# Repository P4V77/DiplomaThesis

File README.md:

# Modular Current Source

## Specifications
### v2.0
- **U<sub>IN</sub>** = 12 - 48V
- **I<sub>OUT_DC</sub>** = &plusmn;10 A (max output power limited by PTC fuses to 144W/48V, current is load and input voltage dependent)
- **I<sub>OUT_AC</sub>** = &plusmn;10 A (0 A DC offset, max output power limited by PTC fuses to 144W/48V, current is load and input voltage dependent)
- **Waveforms:**
  - Harmonic with settable DC offset
  - Square with settable DC offset and Duty Cycle <0,100> %
  - Triangle with settable DC offset
- **Default settings:**  
  - I = 0 A
  - DC offset = 0
  - Duty Cycle = 50%
  - Waveform LUT not initialized (DC output set by default)
- **L<sub>load</sub>** at least 100&micro;H, preferably more than 150 &micro;H
- **Communication:**
  - **CAN FD**
    - Baudrate: 500 kb/s
  - **UART**
    - Baudrate: 921 600 Bd
    - 8 data bits
    - 1 stop bit
    - No parity

#### Set New ID
- **Command:** `ID`
- **Data:** Desired ID (0-250)
- **Description:** Sets a new ID for the current source.

**Example:**
```
1ID5  // Sets the ID of the current source to 5
```

#### Set Current
- **Command:** `I`
- **Data:** Desired current as a signed integer in mA (plus sign not allowed)
- **Description:** Sets the current for DC output and amplitude for AC output.

**Examples:**
```
1I650    // Sets current to 650mA for source ID 1
3I-5000  // Sets current to -5A for source ID 3
```

#### Choosing AC/DC Output
- **Commands:**
  - `D` - DC output
  - `A` - AC output
- **Data:**
  - `1` - Enable AC/DC output
  - `0` - Disable output
- **Note:** For AC output, waveform must be chosen first (see "Set Waveform").

**Examples:**
```
1D1  // Enables DC output for source ID 1
4A1  // Enables AC output for source ID 4
```

#### Set Waveform
- **Commands:**
  - `H` - Harmonic waveform
  - `S` - Square waveform
  - `T` - Triangle waveform
- **Data:** Desired frequency in Hz (unsigned integer)
- **Notes:**
  - Zero DC offset, duty cycle defaults to 50% (square)
  - Max waveform frequency from MoSeZ: **6000 Hz** (actual max depends on load)

**Examples:**
```
1H50     // Sets harmonic waveform at 50 Hz for source ID 1
3S6000   // Sets square waveform at 6000 Hz for source ID 3
2T1000   // Sets triangle waveform at 1000 Hz for source ID 2
```

#### Set DC Offset
- **Command:** `O`
- **Data:** Desired DC current offset of alternating current (signed integer in mA, plus sign not allowed)
- **Applicable for:** All AC waveforms

**Examples:**
```
1O650   // Sets DC offset to 650mA for source ID 1
3O-5000 // Sets DC offset to -5A for source ID 3
```

#### Set Duty Cycle (Square Wave Only)
- **Command:** `C`
- **Data:** Desired duty cycle in % (1-99)

**Examples:**
```
1C40  // Sets duty cycle to 40% for source ID 1
3C80  // Sets duty cycle to 80% for source ID 3
```

#### Set Ramp Time (Square Wave Only)
- **Command:** `RT`
- **Data:** Ramp time in percents (unsigned integer)

**Examples:**
```
1RT50  // Sets ramp time of square waveform to 50% (makes triangle waveform) for source ID 1
2RT10 // Sets ramp time of square waveform to 10% for source ID 2
```

#### Set Phase Shift
- **Command:** `F`
- **Data:** Phase shift in degrees (unsigned integer, 0-359)

**Examples:**
```
1F90   // Sets phase shift to 90° for source ID 1
3F180  // Sets phase shift to 180° for source ID 3
```

#### Position Control
- **Command:** `P`
- **Data:**
  - `1` - Enable position control
  - `0` - Disable output
- **Description:** Enables position control for a linear vibrator with position feedback.

**Example:**
```
9P1  // Enables position control for source ID 9
```

#### Set Position Amplitude
- **Command:** `R`
- **Data:** Position amplitude in micrometers (unsigned integer)
- **Constraints:**
  - **Max position offset + amplitude** ≤ 8 mm
  - **Min position offset - amplitude** ≥ 1 mm

**Examples:**
```
1R3500  // Sets position amplitude to 3.5 mm for source ID 1
5R1000  // Sets position amplitude to 1 mm for source ID 5
```

#### Set Position Offset
- **Command:** `V`
- **Data:** Position offset in micrometers (unsigned integer)
- **Constraints:** Same as "Set Position Amplitude"

**Examples:**
```
1V4000  // Sets position offset to 4 mm for source ID 1
5V7000  // Sets position offset to 7 mm for source ID 5
```

#### Start Logging Position to CAN
- **Command:** `CL`
- **Data:**
  - `1` - Start logging
  - `0` - Stop logging
- **Description:** Sends position data every millisecond (ID, actual position, requested position).

**Example:**
```
1CL1  // Starts position logging for source ID 1
```

#### Define Sequence (Whole Period)
- **Command:** `SP`
- **Data:** Duration of the sequence step in whole periods 
- **Description:** Starts defining a new/next sequence command step with a duration measured in whole periods of the waveform.

**Example:**
```
1SP5  // Starts a new sequence step with a duration of 5 whole periods for source ID 1
```

#### Define Sequence (Half Period)
- **Command:** `SH`
- **Data:** Duration of the sequence step in half periods 
- **Description:** Starts defining a new/next sequence command step with a duration measured in half periods of the waveform.

**Example:**
```
2SH10 // Starts a new sequence step with a duration of 10 half periods for source ID 2
```

#### Define Sequence (Milliseconds)
- **Command:** `SW`
- **Data:** Duration of the sequence step in milliseconds 
- **Description:** Starts defining a new/next sequence command step with a duration measured in milliseconds.
**Example:**
```
4SW100 // Starts a new sequence step with a duration of 100 milliseconds for source ID 4
```

#### Stop Filling Current Sequence
- **Command:** `SF`
- **Data:** No data required (value is ignored)
- **Description:** Stops adding commands to the currently being defined sequence step.

**Example:**
```
1SF  // Stops filling the current sequence step for source ID 1
```

#### Start Sequence
- **Command:** `ST`
- **Data:** Any value accepted
- **Description:** Starts the execution of a pre-configured sequence of commands.

**Example:**
```
1ST  // Starts the stored sequence for source ID 1
```

#### Clear All Sequences
- **Command:** `SC`
- **Data:** Any value accepted
- **Description:** Clears all pre-configured sequences of commands.

**Example:**
```
3SC  // Clears all stored sequences for source ID 3
```

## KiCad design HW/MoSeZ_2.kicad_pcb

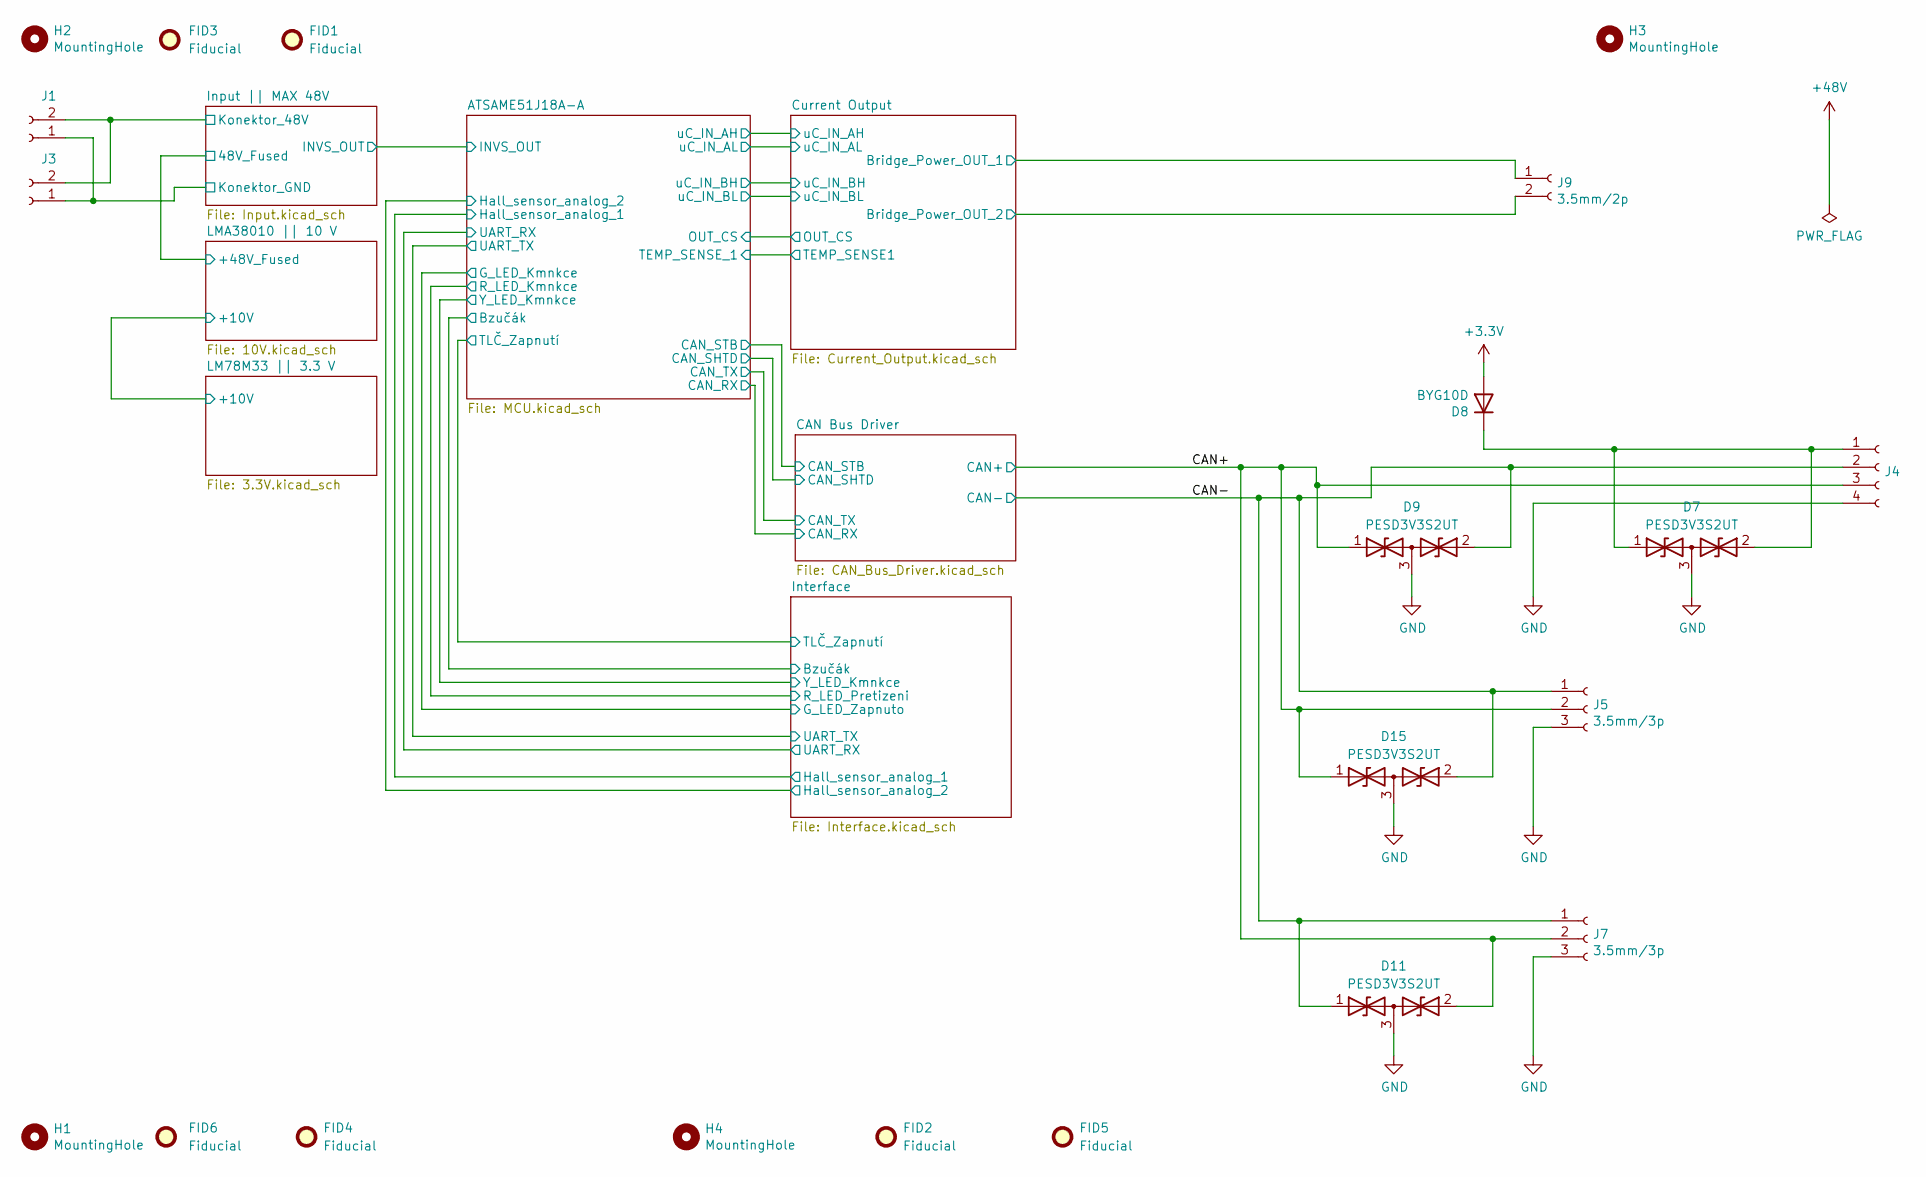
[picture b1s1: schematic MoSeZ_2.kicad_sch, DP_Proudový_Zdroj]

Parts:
D7, D9, D11, D15: PESD3V3S2UT; SOT-23
D8: BYG10D; D_SMA
FID1, FID2, FID3, FID4, FID5, FID6: Fiducial; Fiducial_1mm_Mask2mm
H1, H2, H3, H4: MountingHole; MountingHole_3.5mm_Pad
J1, J3, J9: 3.5mm/2p; PhoenixContact_MC_1,5_2-G-3.5_1x02_P3.50mm_Horizontal
J4: 2.54/4p; PinHeader_1x04_P2.54mm_Vertical
J5, J7: 3.5mm/3p; PhoenixContact_MC_1,5_3-G-3.5_1x03_P3.50mm_Horizontal

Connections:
+3.3V: D8.2 (A); also elsewhere on the board
+48V: J1.2, J3.2; also elsewhere on the board
/CAN+: D9.1 (A1), D11.2 (A2), D15.1 (A1), J4.3, J5.2, J7.2; also elsewhere on the board
/CAN-: D9.2 (A2), D11.1 (A1), D15.2 (A2), J4.2, J5.1, J7.1; also elsewhere on the board
/Current Output/Bridge_Power_OUT_2: J9.2; also elsewhere on the board
/Current Output/DRIVER_1_SW: J9.1; also elsewhere on the board
GND: D7.3 (common), D9.3 (common), D11.3 (common), D15.3 (common), J1.1, J3.1, J4.4, J5.3, J7.3; also elsewhere on the board
unnamed: D7.1 (A1), D7.2 (A2), D8.1 (K), J4.1

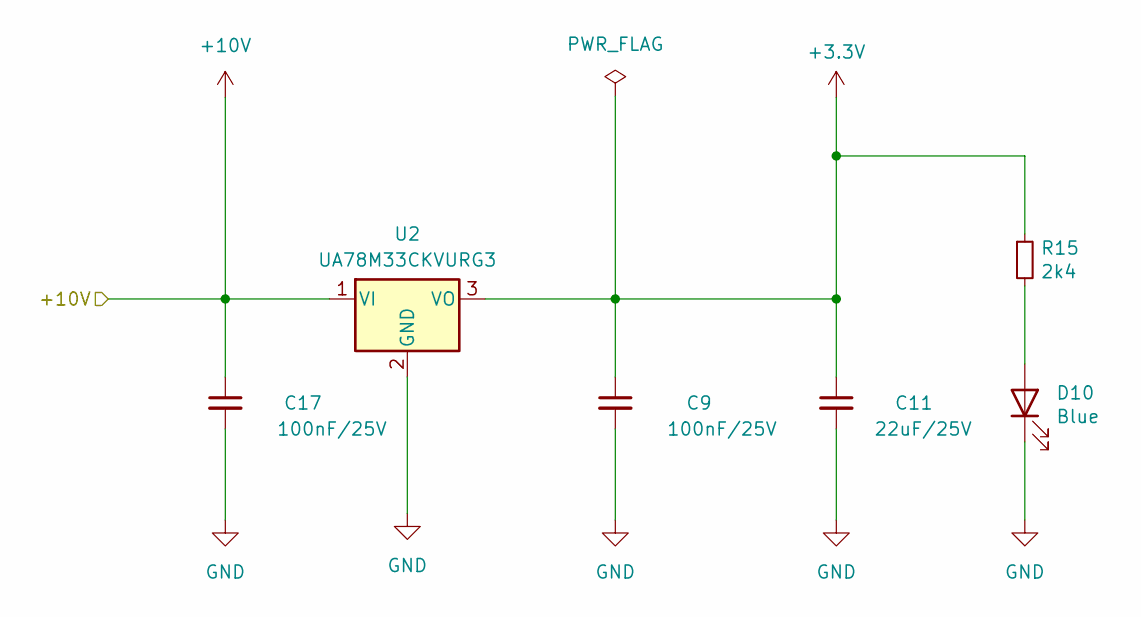
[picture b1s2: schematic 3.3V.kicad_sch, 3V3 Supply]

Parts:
C9, C17: 100nF/25V; C_0603_1608Metric
C11: 22uF/25V; C_0805_2012Metric
D10: Blue; D_0603_1608Metric
R15: 2k4; R_0603_1608Metric
U2: UA78M33CKVURG3; TO-252-2

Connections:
+3.3V: C9.1, C11.1, R15.1, U2.3 (VO); also elsewhere on the board
+10V: C17.1, U2.1 (VI); also elsewhere on the board
GND: C9.2, C11.2, C17.2, D10.1 (K), U2.2 (GND); also elsewhere on the board
unnamed: D10.2 (A), R15.2

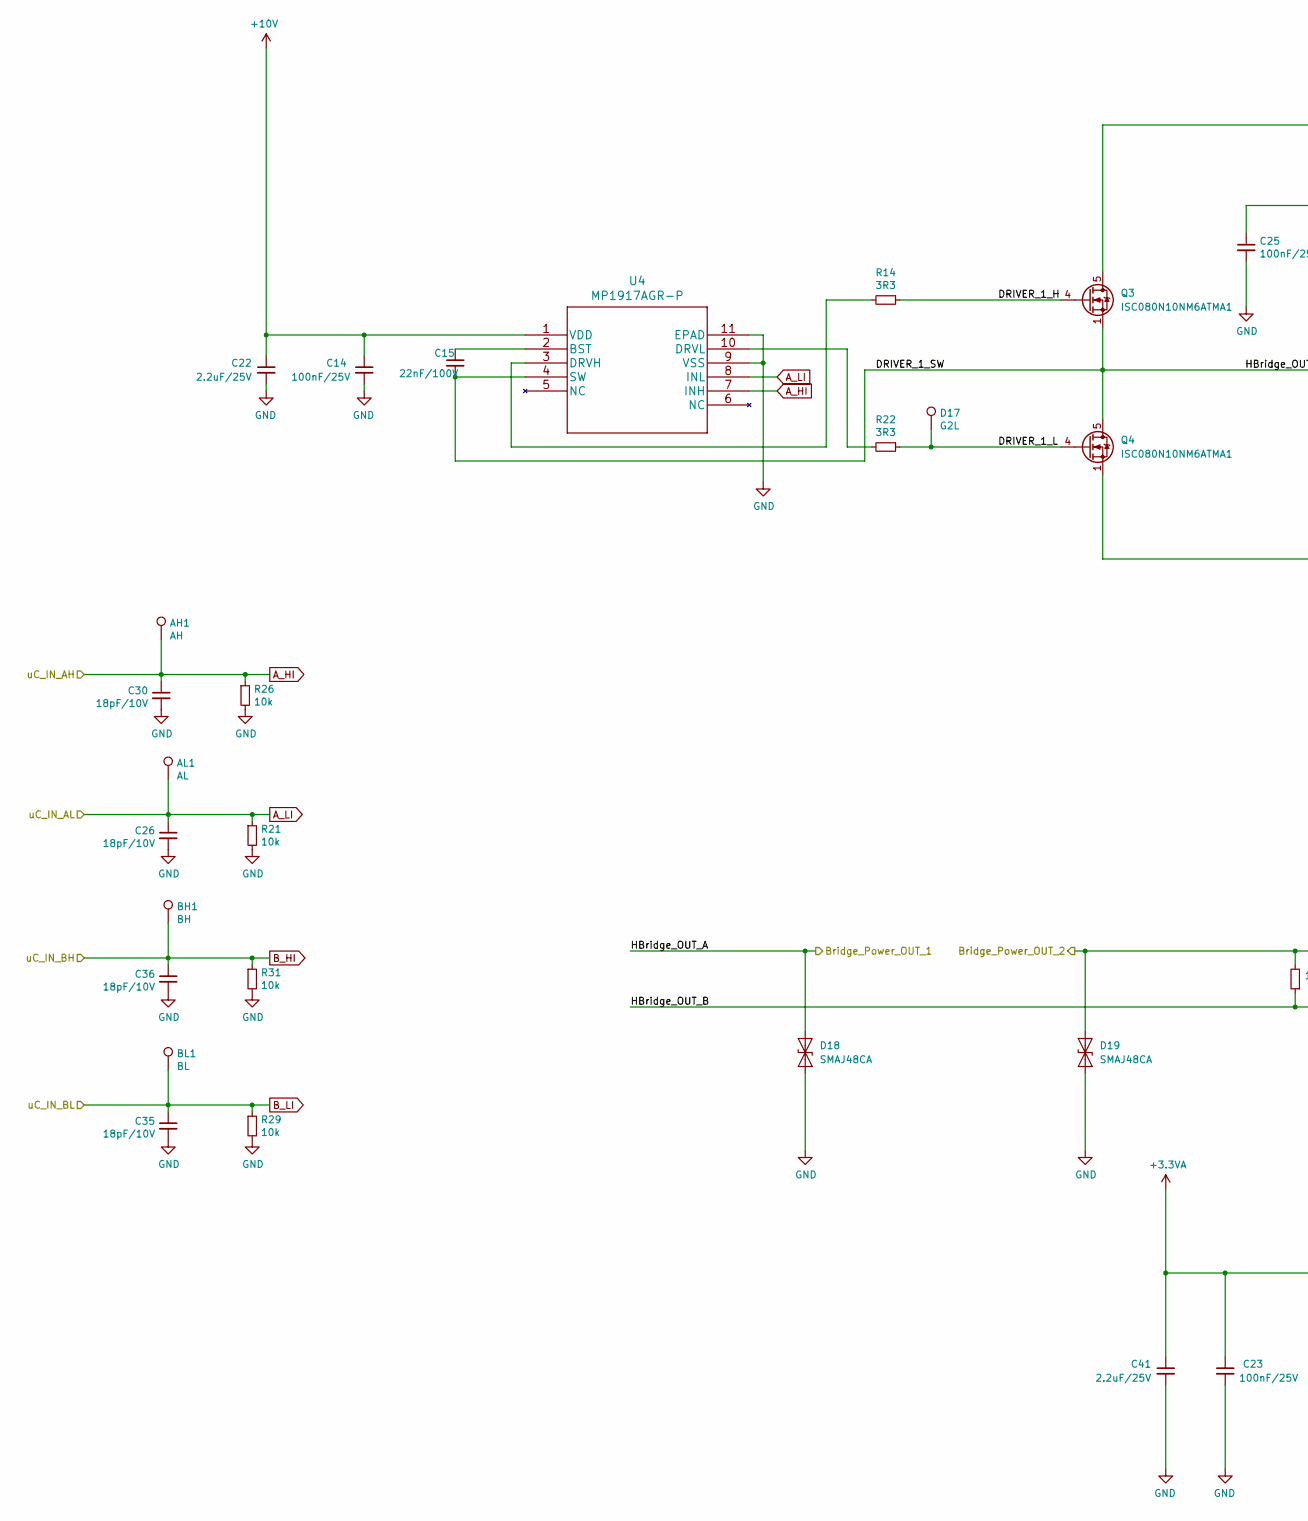
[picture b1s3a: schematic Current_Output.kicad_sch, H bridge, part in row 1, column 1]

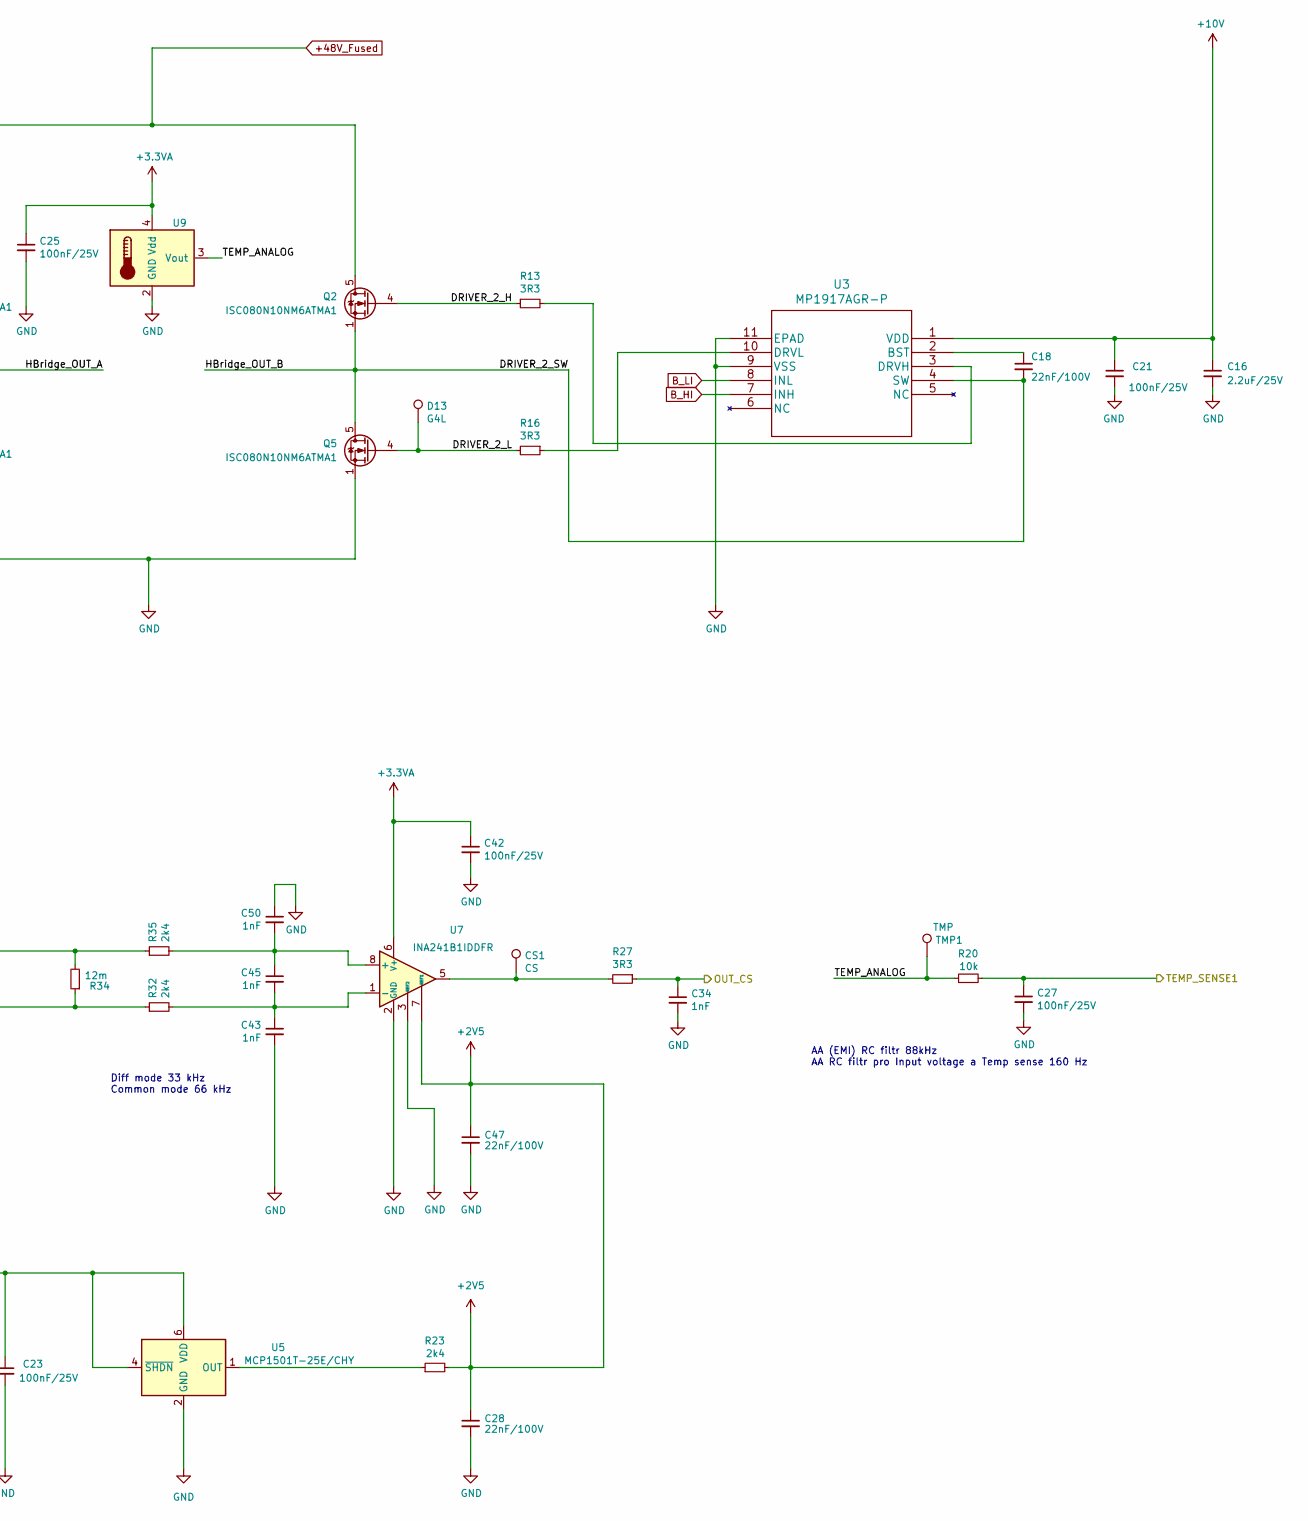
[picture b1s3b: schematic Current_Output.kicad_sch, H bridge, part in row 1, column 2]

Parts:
AH1: AH; TestPoint_Pad_1.5x1.5mm
AL1: AL; TestPoint_Pad_1.5x1.5mm
BH1: BH; TestPoint_Pad_1.5x1.5mm
BL1: BL; TestPoint_Pad_1.5x1.5mm
C14, C21, C23, C25, C27, C42: 100nF/25V; C_0603_1608Metric
C15, C18, C28, C47: 22nF/100V; C_0603_1608Metric
C16, C22, C41: 2.2uF/25V; C_0805_2012Metric
C26, C30, C35, C36: 18pF/10V; C_0603_1608Metric
C34, C43, C45, C50: 1nF; C_0603_1608Metric
CS1: CS; TestPoint_Pad_1.5x1.5mm
D13: G4L; TestPoint_Pad_1.5x1.5mm
D17: G2L; TestPoint_Pad_1.5x1.5mm
D18, D19: SMAJ48CA; D_SMA
Q2, Q3, Q4, Q5: ISC080N10NM6ATMA1; Infineon_PG-TDSON-8_6.15x5.15mm
R13, R14, R16, R22, R27: 3R3; R_0805_2012Metric
R20, R21, R26, R29, R31: 10k; R_0603_1608Metric
R23, R32, R35: 2k4; R_0603_1608Metric
R34: 12m; R_2512_6332Metric
TMP1: TMP; TestPoint_Pad_1.5x1.5mm
U3, U4: MP1917AGR-P; QFN-4x4_MP1917A_MNP
U5: MCP1501T-25E/CHY; SOT-23-6
U7: INA241B1IDDFR; TSOT-23-8
U9: MCP9700T-ELT; SOT-353_SC-70-5

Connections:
+2V5: C28.1, C47.1, R23.2, U7.7 (REF1); also elsewhere on the board
+3.3VA: C23.1, C25.1, C41.1, C42.1, U5.4 (~SHDN), U5.6 (VDD), U7.6 (V+), U9.4 (Vdd); also elsewhere on the board
+10V: C14.1, C16.1, C21.1, C22.1, U3.1 (VDD), U4.1 (VDD); also elsewhere on the board
+48V_Fused: Q2.5 (D), Q3.5 (D); also elsewhere on the board
/ATSAME51J18A-A/OUT_CS: C34.1, R27.1; also elsewhere on the board
/ATSAME51J18A-A/TEMP_SENSE_1: C27.1, R20.2; also elsewhere on the board
/Current Output/Bridge_Power_OUT_2: D19.2 (A2), R34.2, R35.1; also elsewhere on the board
/Current Output/DRIVER_1_H: Q3.4 (G), R14.1
/Current Output/DRIVER_1_L: D17.1, Q4.4 (G), R22.1
/Current Output/DRIVER_1_SW: C15.2, D18.2 (A2), Q3.1 (S), Q3.2 (S), Q3.3 (S), Q4.5 (D), U4.4 (SW); also elsewhere on the board
/Current Output/DRIVER_2_H: Q2.4 (G), R13.1
/Current Output/DRIVER_2_L: D13.1, Q5.4 (G), R16.2
/Current Output/DRIVER_2_SW: C18.2, Q2.1 (S), Q2.2 (S), Q2.3 (S), Q5.5 (D), R32.1, R34.1, U3.4 (SW)
/Current Output/TEMP_ANALOG: R20.1, TMP1.1, U9.3 (Vout)
A_HI: AH1.1, C30.1, R26.1, U4.7 (INH); also elsewhere on the board
A_LI: AL1.1, C26.1, R21.1, U4.8 (INL); also elsewhere on the board
B_HI: BH1.1, C36.1, R31.1, U3.7 (INH); also elsewhere on the board
B_LI: BL1.1, C35.1, R29.1, U3.8 (INL); also elsewhere on the board
GND: C14.2, C16.2, C21.2, C22.2, C23.2, C25.2, C26.2, C27.2, C28.2, C30.2, C34.2, C35.2, C36.2, C41.2, C42.2, C43.2, C47.2, C50.1, D18.1 (A1), D19.1 (A1), Q4.1 (S), Q4.2 (S), Q4.3 (S), Q5.1 (S), Q5.2 (S), Q5.3 (S), R21.2, R26.2, R29.2, R31.2, U3.9 (VSS), U3.11 (EPAD), U4.9 (VSS), U4.11 (EPAD), U5.2 (GND), U5.3 (GND), U5.5 (GND), U7.2 (GND), U7.3 (REF2), U7.4 (GND), U9.2 (GND); also elsewhere on the board
unnamed: CS1.1, R27.2, U7.5
unnamed: C18.1, U3.2 (BST)
unnamed: R13.2, U3.3 (DRVH)
unnamed: R16.1, U3.10 (DRVL)
unnamed: C15.1, U4.2 (BST)
unnamed: R14.2, U4.3 (DRVH)
unnamed: R22.2, U4.10 (DRVL)
unnamed: R23.1, U5.1 (OUT)
unnamed: C45.1, C50.2, R35.2, U7.8 (+)
unnamed: C43.1, C45.2, R32.2, U7.1 (-)

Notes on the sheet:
Diff mode 33 kHz Common mode 66 kHz
AA (EMI) RC filtr 88kHz AA RC filtr pro Input voltage a Temp sense 160 Hz

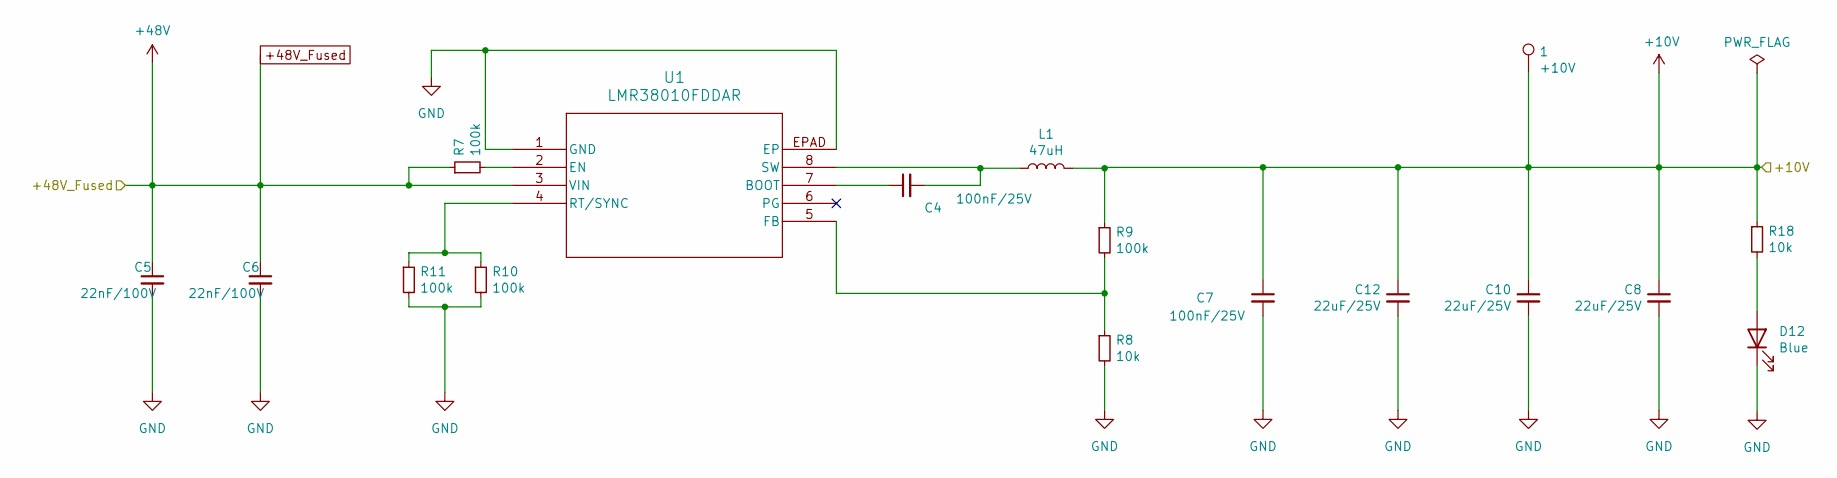
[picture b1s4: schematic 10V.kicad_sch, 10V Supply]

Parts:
1: +10V; TestPoint_Pad_1.5x1.5mm
C4, C7: 100nF/25V; C_0603_1608Metric
C5, C6: 22nF/100V; C_0603_1608Metric
C8, C10, C12: 22uF/25V; C_0805_2012Metric
D12: Blue; D_0603_1608Metric
L1: 47uH; L_Cenker_CKCS6045
R7, R9, R10, R11: 100k; R_0603_1608Metric
R8, R18: 10k; R_0603_1608Metric
U1: LMR38010FDDAR; LMR38010FDDAR_TEX-L

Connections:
+10V: 1.1, C7.1, C8.1, C10.1, C12.1, L1.2, R9.1, R18.1; also elsewhere on the board
+48V_Fused: C5.1, C6.1, R7.1, U1.3 (VIN); also elsewhere on the board
GND: C5.2, C6.2, C7.2, C8.2, C10.2, C12.2, D12.1 (K), R8.2, R10.2, R11.2, U1.1 (GND), U1.EPAD (EP); also elsewhere on the board
unnamed: D12.2 (A), R18.2
unnamed: C4.1, U1.7 (BOOT)
unnamed: R7.2, U1.2 (EN)
unnamed: R8.1, R9.2, U1.5 (FB)
unnamed: R10.1, R11.1, U1.4 (RT/SYNC)
unnamed: C4.2, L1.1, U1.8 (SW)

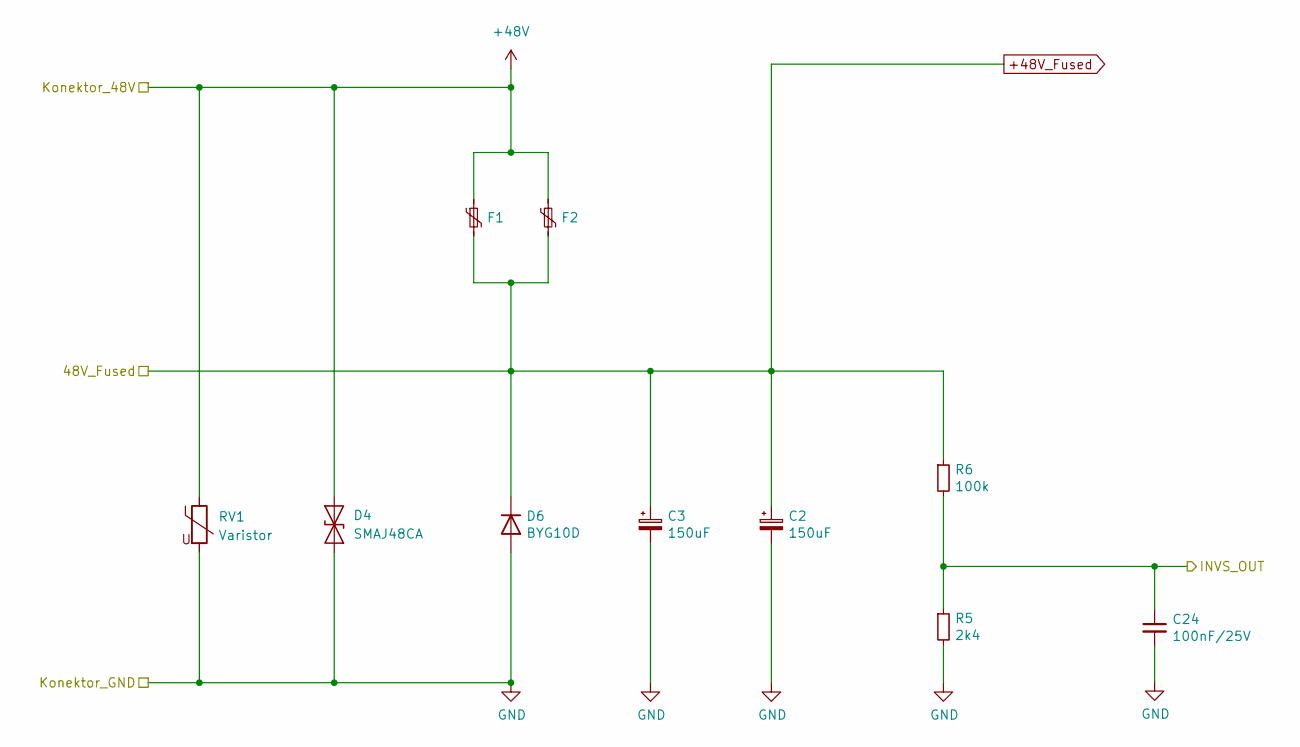
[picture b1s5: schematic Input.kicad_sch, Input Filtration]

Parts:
C2, C3: 150uF; CP_Radial_D10.0mm_P5.00mm
C24: 100nF/25V; C_0603_1608Metric
D4: SMAJ48CA; D_SMA
D6: BYG10D; D_SMA
F1, F2: 2920L150/60MR; Fuse_2920_7451Metric
R5: 2k4; R_0603_1608Metric
R6: 100k; R_0603_1608Metric
RV1: Varistor; R_0805_2012Metric

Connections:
+48V: D4.2 (A2), F1.1, F2.1, RV1.1; also elsewhere on the board
+48V_Fused: C2.1, C3.1, D6.1 (K), F1.2, F2.2, R6.1; also elsewhere on the board
/ATSAME51J18A-A/INVS_OUT: C24.1, R5.1, R6.2; also elsewhere on the board
GND: C2.2, C3.2, C24.2, D4.1 (A1), D6.2 (A), R5.2, RV1.2; also elsewhere on the board

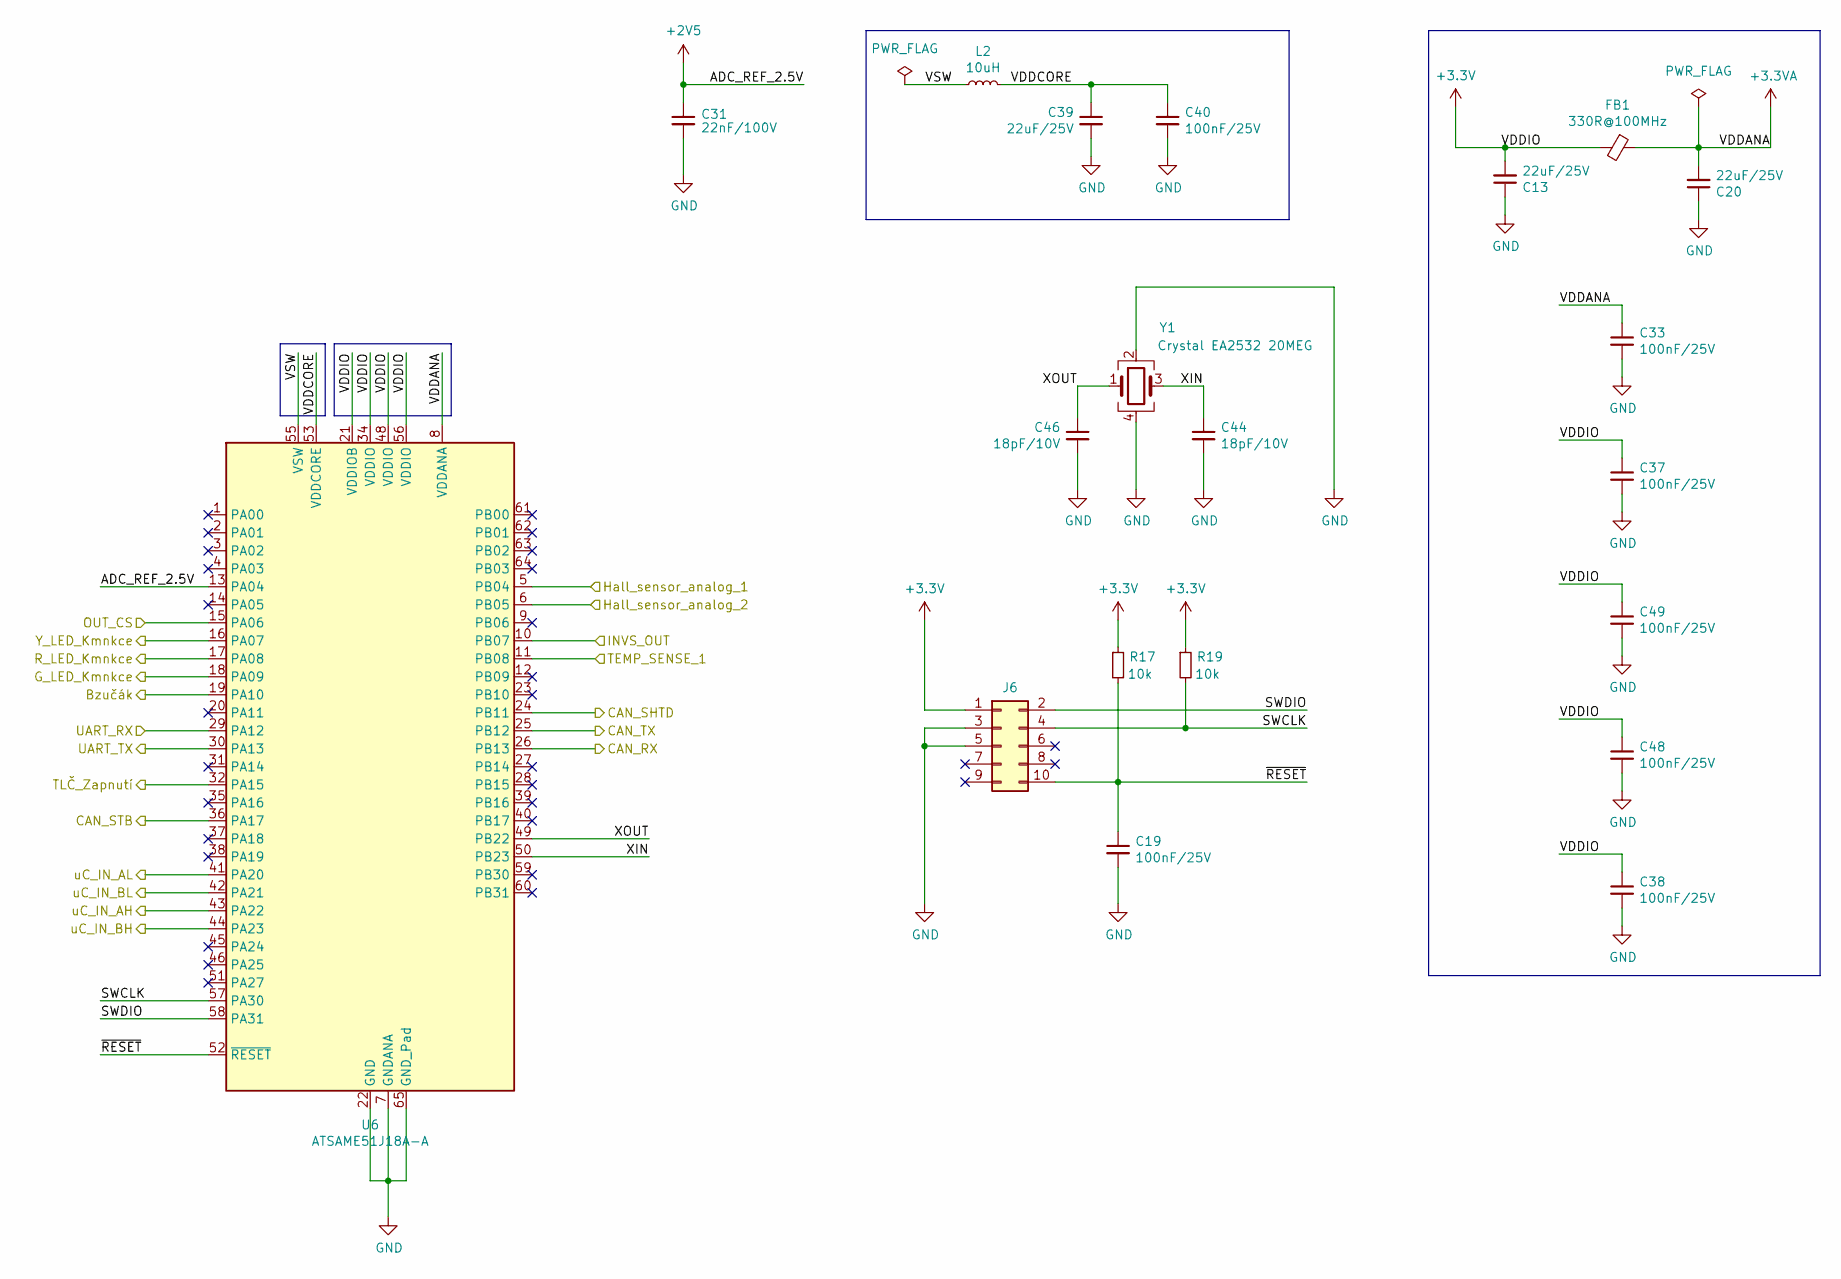
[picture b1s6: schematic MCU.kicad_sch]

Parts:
C13, C20, C39: 22uF/25V; C_0805_2012Metric
C19, C33, C37, C38, C40, C48, C49: 100nF/25V; C_0603_1608Metric
C31: 22nF/100V; C_0603_1608Metric
C44, C46: 18pF/10V; C_0603_1608Metric
FB1: 330R@100MHz; L_0805_2012Metric
J6: PRG_Kon; PinHeader_2x05_P1.27mm_Vertical
L2: 10uH; L_Wuerth_MAPI-2010
R17, R19: 10k; R_0603_1608Metric
U6: ATSAME51J18A-A; QFN-64-1EP_9x9mm_P0.5mm_EP4.7x4.7mm
Y1: Crystal EA2532 20MEG; Crystal_SMD_EuroQuartz_MT-4Pin_3.2x2.5mm

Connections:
+2V5: C31.1, U6.13 (PA04); also elsewhere on the board
+3.3V: C13.2, C37.1, C38.1, C48.1, C49.1, FB1.2, J6.1, R17.1, R19.1, U6.21 (VDDIOB), U6.34 (VDDIO), U6.48 (VDDIO), U6.56 (VDDIO); also elsewhere on the board
+3.3VA: C20.2, C33.1, FB1.1, U6.8 (VDDANA); also elsewhere on the board
/ATSAME51J18A-A/Bzučák: U6.19 (PA10); also elsewhere on the board
/ATSAME51J18A-A/CAN_RX: U6.26 (PB13); also elsewhere on the board
/ATSAME51J18A-A/CAN_SHTD: U6.24 (PB11); also elsewhere on the board
/ATSAME51J18A-A/CAN_STB: U6.36 (PA17); also elsewhere on the board
/ATSAME51J18A-A/CAN_TX: U6.25 (PB12); also elsewhere on the board
/ATSAME51J18A-A/G_LED_Kmnkce: U6.18 (PA09); also elsewhere on the board
/ATSAME51J18A-A/Hall_sensor_analog_1: U6.5 (PB04); also elsewhere on the board
/ATSAME51J18A-A/Hall_sensor_analog_2: U6.6 (PB05); also elsewhere on the board
/ATSAME51J18A-A/INVS_OUT: U6.10 (PB07); also elsewhere on the board
/ATSAME51J18A-A/OUT_CS: U6.15 (PA06); also elsewhere on the board
/ATSAME51J18A-A/R_LED_Kmnkce: U6.17 (PA08); also elsewhere on the board
/ATSAME51J18A-A/SWCLK: J6.4, R19.2, U6.57 (PA30)
/ATSAME51J18A-A/SWDIO: J6.2, U6.58 (PA31)
/ATSAME51J18A-A/TEMP_SENSE_1: U6.11 (PB08); also elsewhere on the board
/ATSAME51J18A-A/TLČ_Zapnutí: U6.32 (PA15); also elsewhere on the board
/ATSAME51J18A-A/UART_RX: U6.29 (PA12); also elsewhere on the board
/ATSAME51J18A-A/UART_TX: U6.30 (PA13); also elsewhere on the board
/ATSAME51J18A-A/VDDCORE: C39.1, C40.1, L2.2, U6.53 (VDDCORE)
/ATSAME51J18A-A/VSW: L2.1, U6.55 (VSW)
/ATSAME51J18A-A/XIN: C44.1, U6.50 (PB23), Y1.3
/ATSAME51J18A-A/XOUT: C46.1, U6.49 (PB22), Y1.1
/ATSAME51J18A-A/Y_LED_Kmnkce: U6.16 (PA07); also elsewhere on the board
/ATSAME51J18A-A/~RESET: C19.1, J6.10, R17.2, U6.52 (~RESET)
A_HI: U6.43 (PA22); also elsewhere on the board
A_LI: U6.41 (PA20); also elsewhere on the board
B_HI: U6.44 (PA23); also elsewhere on the board
B_LI: U6.42 (PA21); also elsewhere on the board
GND: C13.1, C19.2, C20.1, C31.2, C33.2, C37.2, C38.2, C39.2, C40.2, C44.2, C46.2, C48.2, C49.2, J6.3, J6.5, U6.7 (GNDANA), U6.22 (GND), U6.33 (GND), U6.47 (GND), U6.54 (GND), U6.65 (GND_Pad), Y1.2, Y1.4; also elsewhere on the board

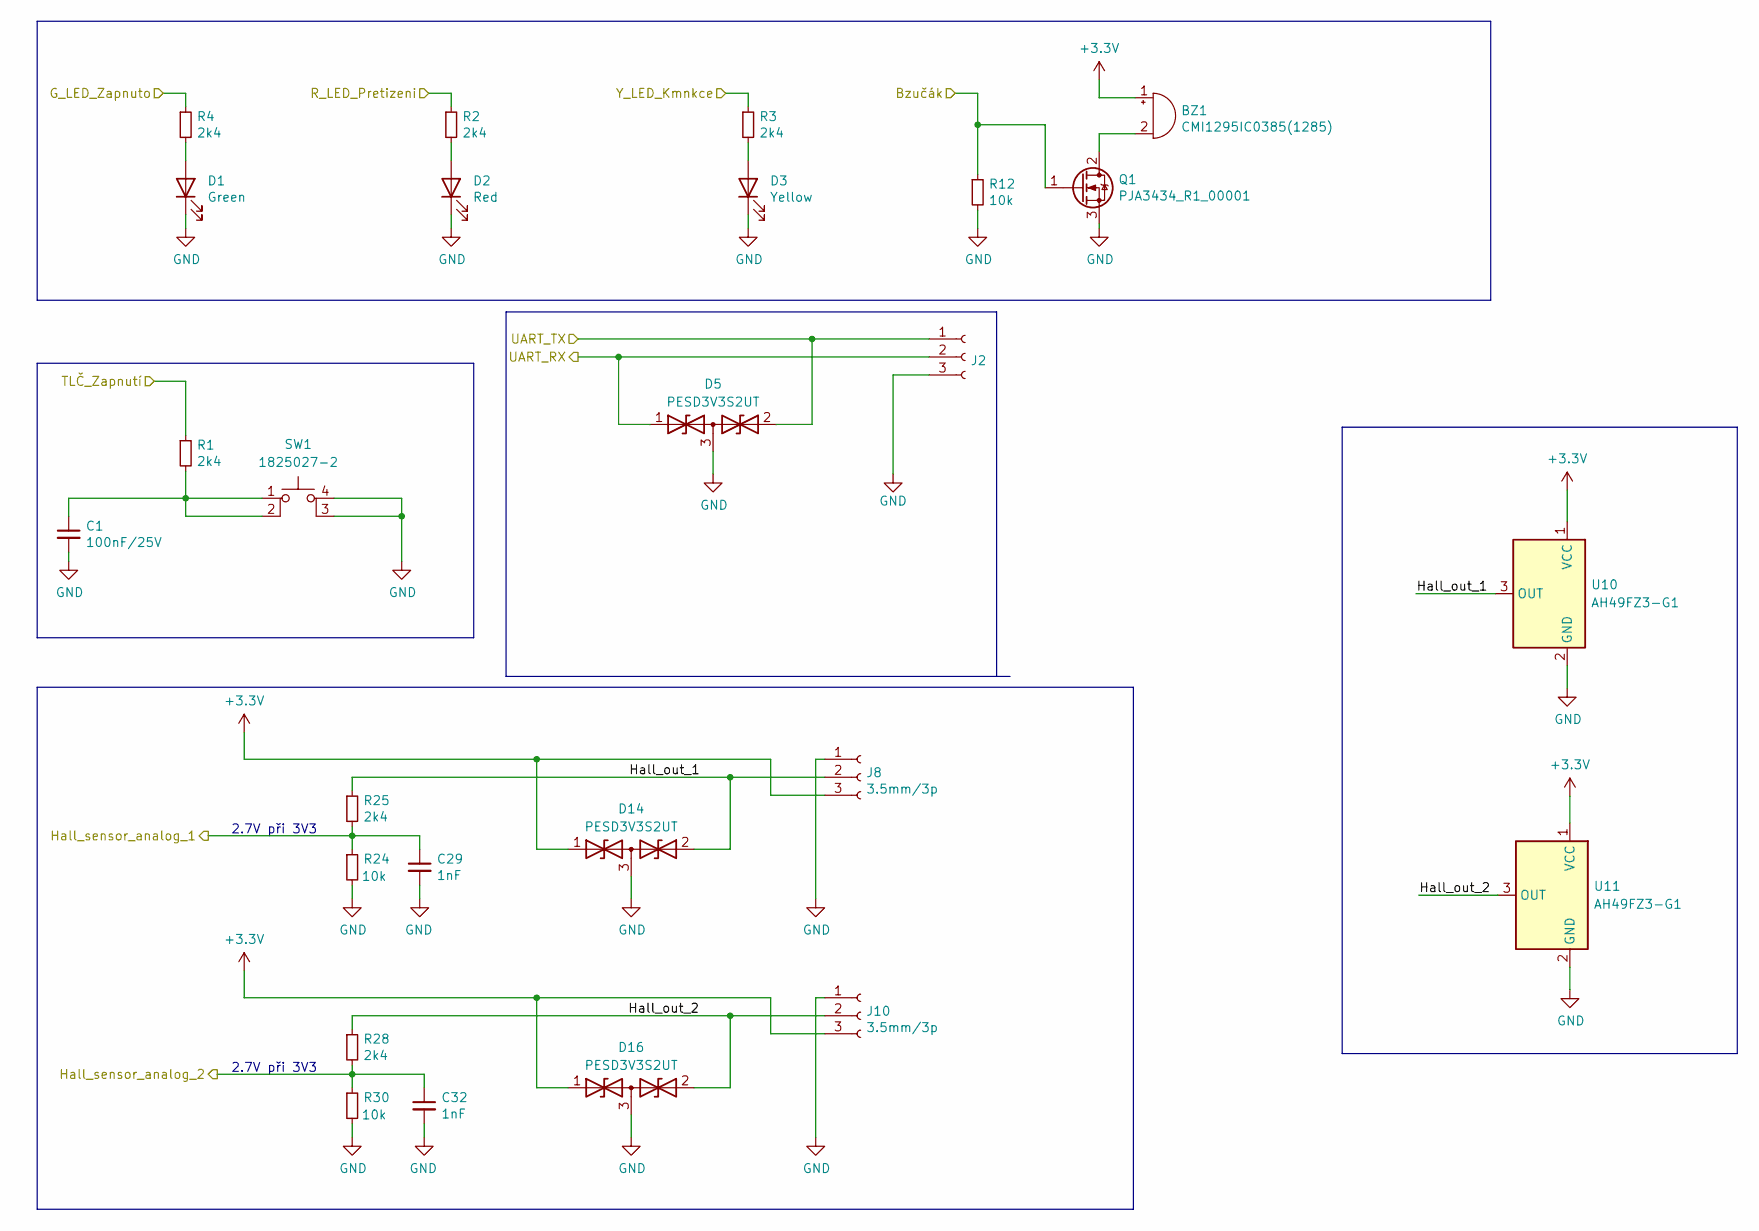
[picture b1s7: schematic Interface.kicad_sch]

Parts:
BZ1: CMI1295IC0385(1285); Buzzer_12x9.5RM7.6
C1: 100nF/25V; C_0603_1608Metric
C29, C32: 1nF; C_0603_1608Metric
D1: Green; D_0603_1608Metric
D2: Red; D_0603_1608Metric
D3: Yellow; D_0603_1608Metric
D5, D14, D16: PESD3V3S2UT; SOT-23
J2: 2.54mm/3p; PinHeader_1x03_P2.54mm_Vertical
J8, J10: 3.5mm/3p; PhoenixContact_MC_1,5_3-G-3.5_1x03_P3.50mm_Horizontal
Q1: PJA3434_R1_00001; SOT-23-3
R1, R2, R3, R4, R25, R28: 2k4; R_0603_1608Metric
R12, R24, R30: 10k; R_0603_1608Metric
SW1: 1825027-2; SW_Tactile_SPST_Angled_PTS645Vx39-2LFS
U10, U11: AH49FZ3-G1; TO-92_Inline

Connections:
+3.3V: BZ1.1 (-), D14.1 (A1), D16.1 (A1), J8.3, J10.3, U10.1 (VCC), U11.1 (VCC); also elsewhere on the board
/ATSAME51J18A-A/Bzučák: Q1.1 (G), R12.1; also elsewhere on the board
/ATSAME51J18A-A/G_LED_Kmnkce: R4.1; also elsewhere on the board
/ATSAME51J18A-A/Hall_sensor_analog_1: C29.1, R24.1, R25.2; also elsewhere on the board
/ATSAME51J18A-A/Hall_sensor_analog_2: C32.1, R28.2, R30.1; also elsewhere on the board
/ATSAME51J18A-A/R_LED_Kmnkce: R2.1; also elsewhere on the board
/ATSAME51J18A-A/TLČ_Zapnutí: R1.1; also elsewhere on the board
/ATSAME51J18A-A/UART_RX: D5.1 (A1), J2.2; also elsewhere on the board
/ATSAME51J18A-A/UART_TX: D5.2 (A2), J2.1; also elsewhere on the board
/ATSAME51J18A-A/Y_LED_Kmnkce: R3.1; also elsewhere on the board
/Interface/Hall_out_1: D14.2 (A2), J8.2, R25.1, U10.3 (OUT)
/Interface/Hall_out_2: D16.2 (A2), J10.2, R28.1, U11.3 (OUT)
GND: C1.2, C29.2, C32.2, D1.1 (K), D2.1 (K), D3.1 (K), D5.3 (common), D14.3 (common), D16.3 (common), J2.3, J8.1, J10.1, Q1.3 (S), R12.2, R24.2, R30.2, SW1.3 (K), SW1.4 (A), U10.2 (GND), U11.2 (GND); also elsewhere on the board
unnamed: BZ1.2 (+), Q1.2 (D)
unnamed: C1.1, R1.2, SW1.1, SW1.2
unnamed: D1.2 (A), R4.2
unnamed: D2.2 (A), R2.2
unnamed: D3.2 (A), R3.2

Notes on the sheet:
2.7V při 3V3

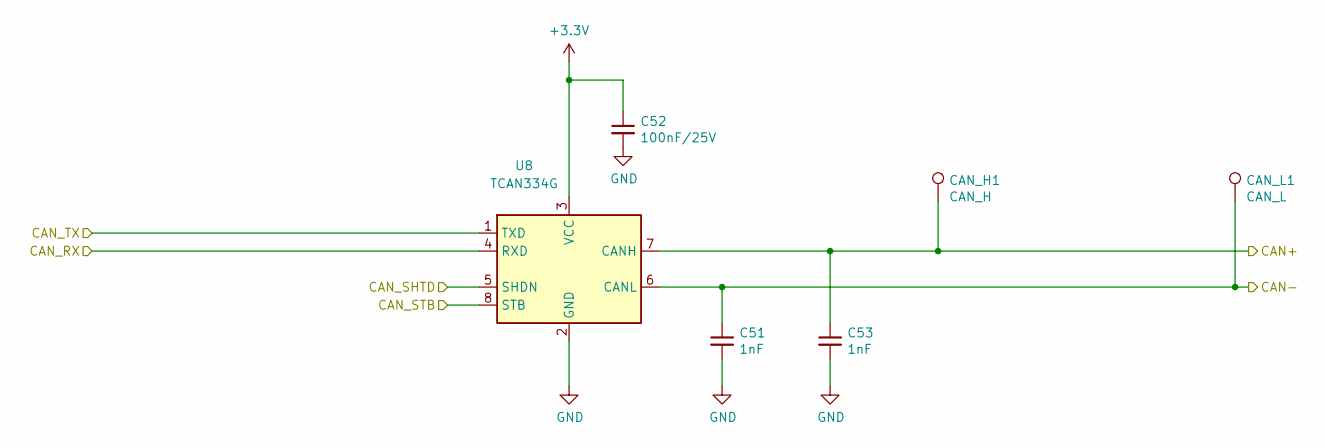
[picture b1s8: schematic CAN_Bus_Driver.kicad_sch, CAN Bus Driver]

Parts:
C51, C53: 1nF; C_0603_1608Metric
C52: 100nF/25V; C_0603_1608Metric
CAN_H1: CAN_H; TestPoint_Pad_1.5x1.5mm
CAN_L1: CAN_L; TestPoint_Pad_1.5x1.5mm
U8: TCAN334G; SOT-23-8

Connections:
+3.3V: C52.1, U8.3 (VCC); also elsewhere on the board
/ATSAME51J18A-A/CAN_RX: U8.4 (RXD); also elsewhere on the board
/ATSAME51J18A-A/CAN_SHTD: U8.5 (SHDN); also elsewhere on the board
/ATSAME51J18A-A/CAN_STB: U8.8 (STB); also elsewhere on the board
/ATSAME51J18A-A/CAN_TX: U8.1 (TXD); also elsewhere on the board
/CAN+: C53.1, CAN_H1.1, U8.7 (CANH); also elsewhere on the board
/CAN-: C51.1, CAN_L1.1, U8.6 (CANL); also elsewhere on the board
GND: C51.2, C52.2, C53.2, U8.2 (GND); also elsewhere on the board
